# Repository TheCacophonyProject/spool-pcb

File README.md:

# Spool PCB

## Other bits to order

### DigiKey

- 2 x Crimped leads: [455-4118-ND](https://www.digikey.com/en/products/detail/jst-sales-america-inc/ASXASXA22K254/9951627) Can chop in half and use 2 of the ends for the motor and 2 for the magnet
- 1 x 8 Pin cable assembly [455-3842-ND](https://www.digikey.com/en/products/detail/jst-sales-america-inc/A08XAF08XAF22K203B/9922118) for connecting main and plug board.
- 3 x Protection Diodes [SS54-HF](https://www.digikey.com/en/products/detail/comchip-technology/SS54-HF/11584321) to be hand soldered onto the plug board.

### LCSC

- 2 x Photo interrupter [DY-ITR8402](https://www.lcsc.com/product-detail/C390039.html)
- 1 x 2 Pin JST XA housing [XAP-02V-1](https://www.lcsc.com/product-detail/C157892.html)
- 1 x 3 Pin JST XA housing [XAP-03V-1](https://www.lcsc.com/product-detail/C157891.html)
- 2 x 8 Pin JST XA Plug [S08B-XASK-1(LF)(SN)](https://www.lcsc.com/product-detail/C495695.html)
- 1 x Magnet rotary position sensor? Not too sure if this will end up being used or not. [AS5600-ASOT](https://www.lcsc.com/product-detail/C499458.html)

### JNICON

- 1 x 6 Pin Auxiliary plug (TODO: Add part number)
- 1 x 4 Pin Power plug (TODO: Add part number)

## Construction

TODO: Write construction/programming instructions.

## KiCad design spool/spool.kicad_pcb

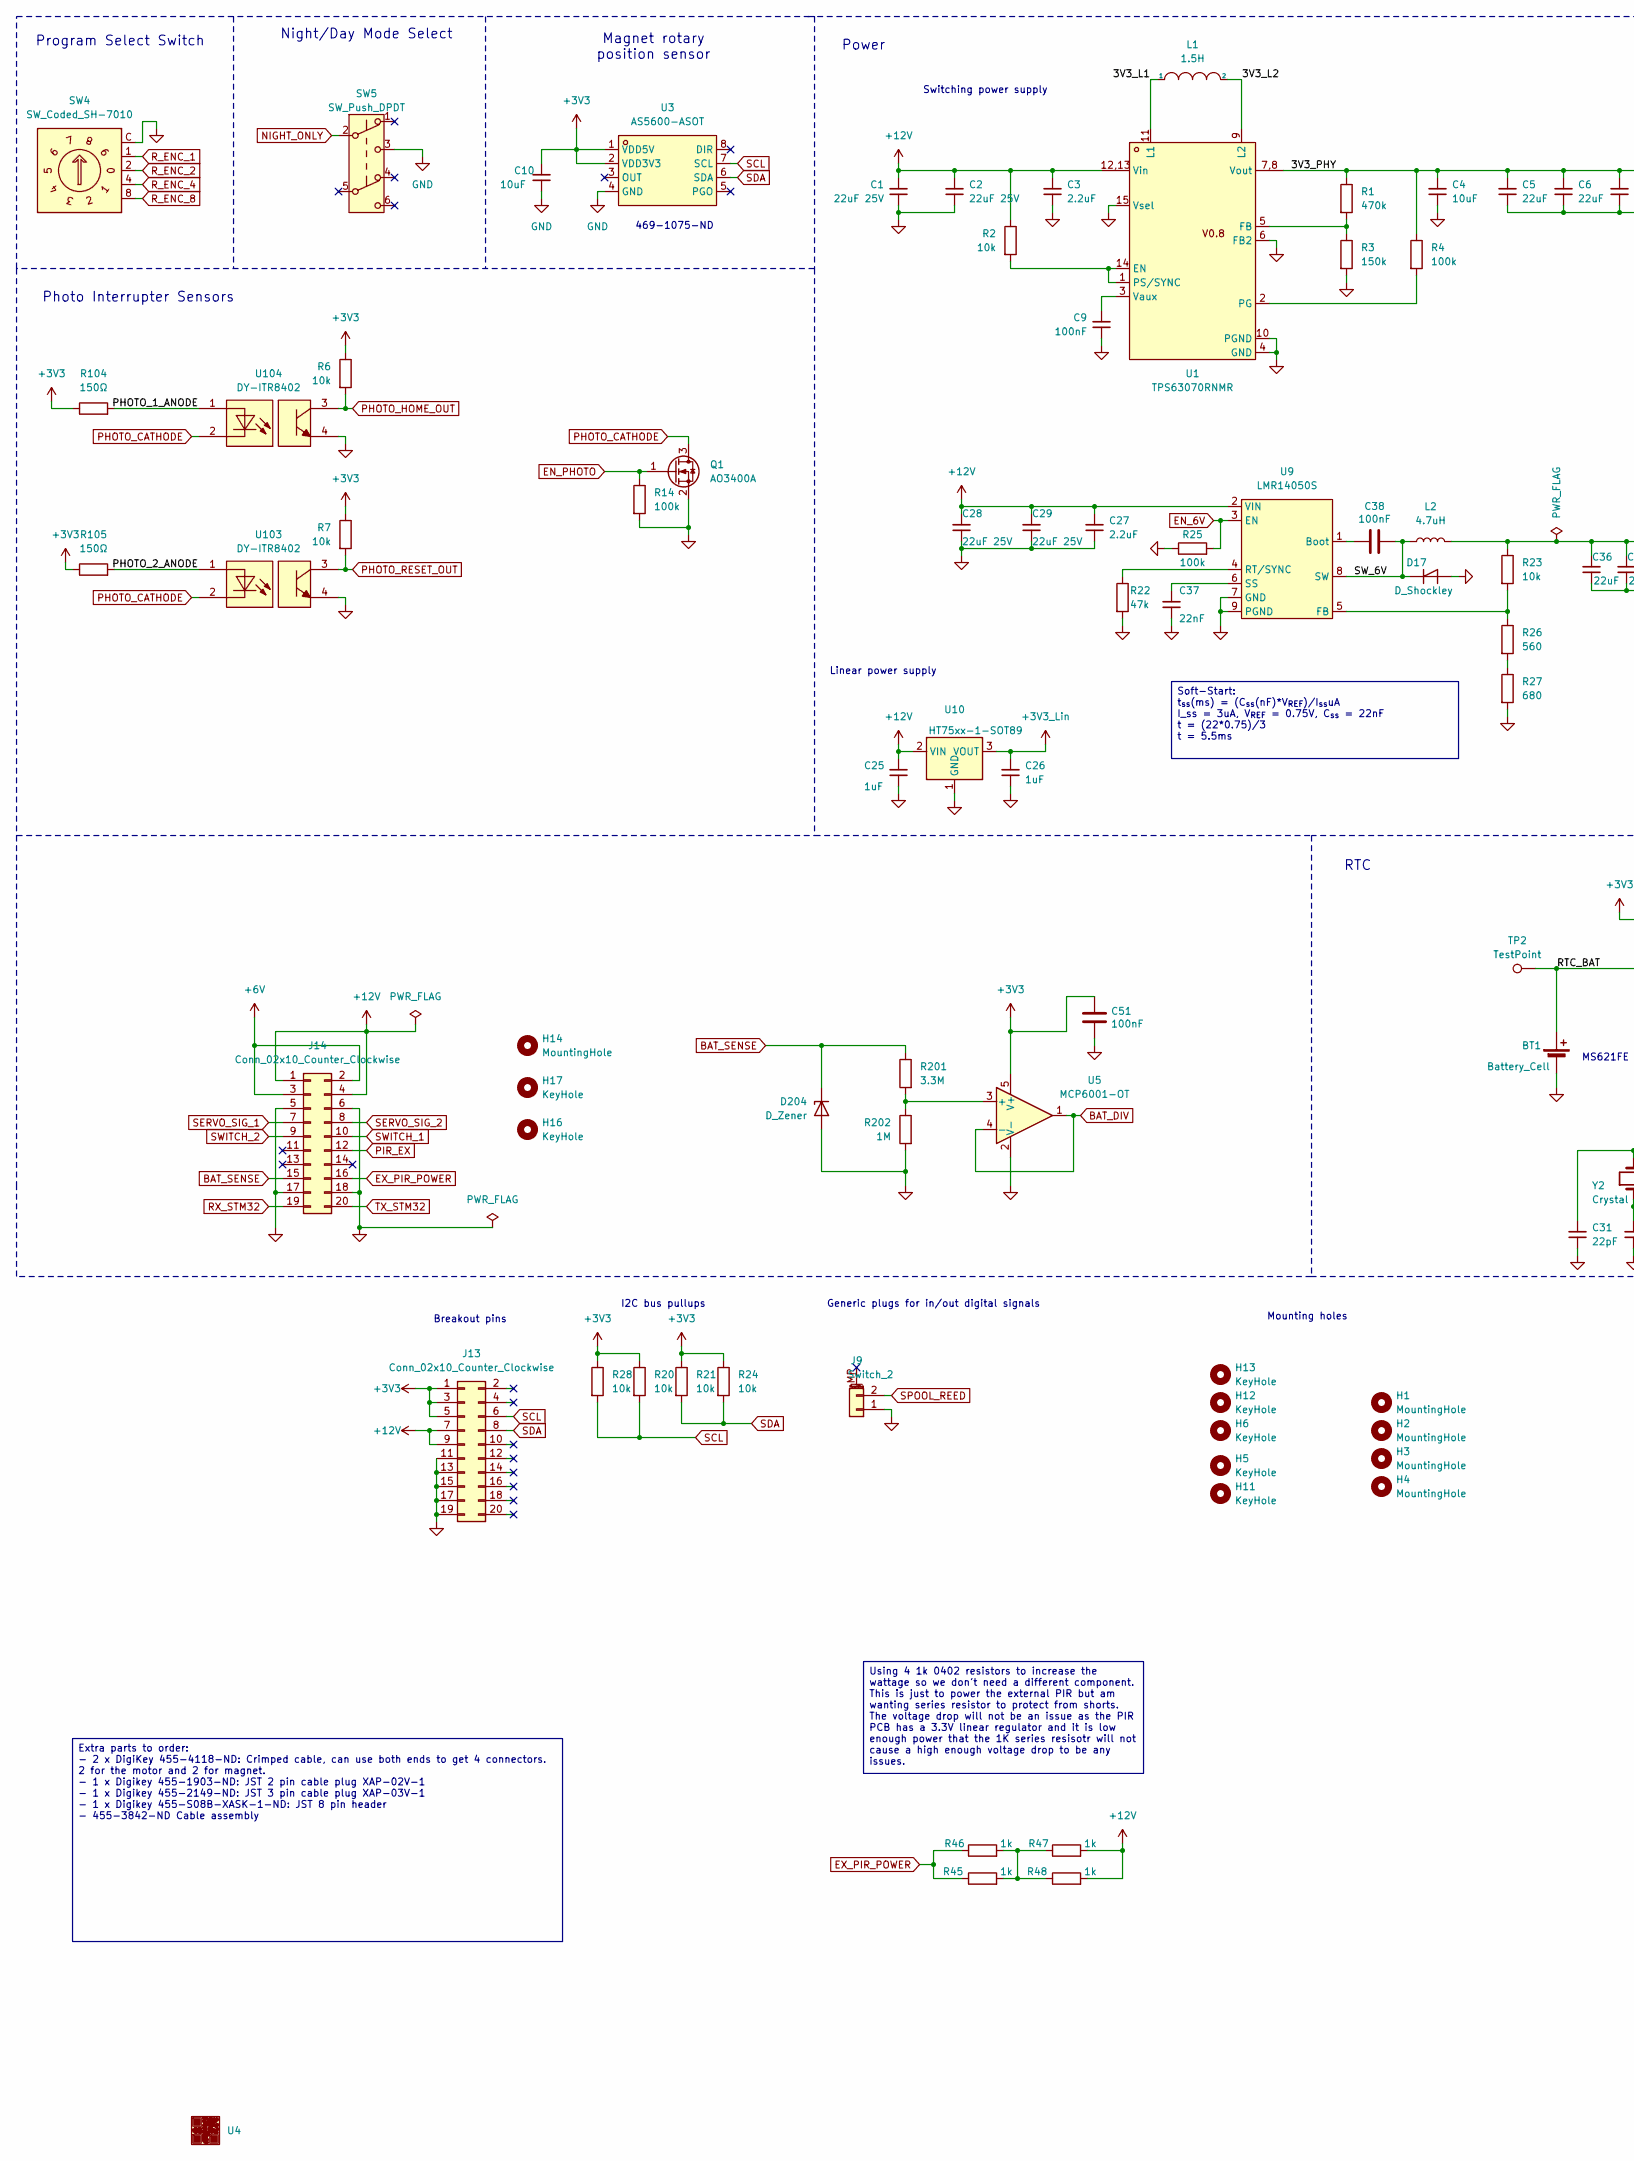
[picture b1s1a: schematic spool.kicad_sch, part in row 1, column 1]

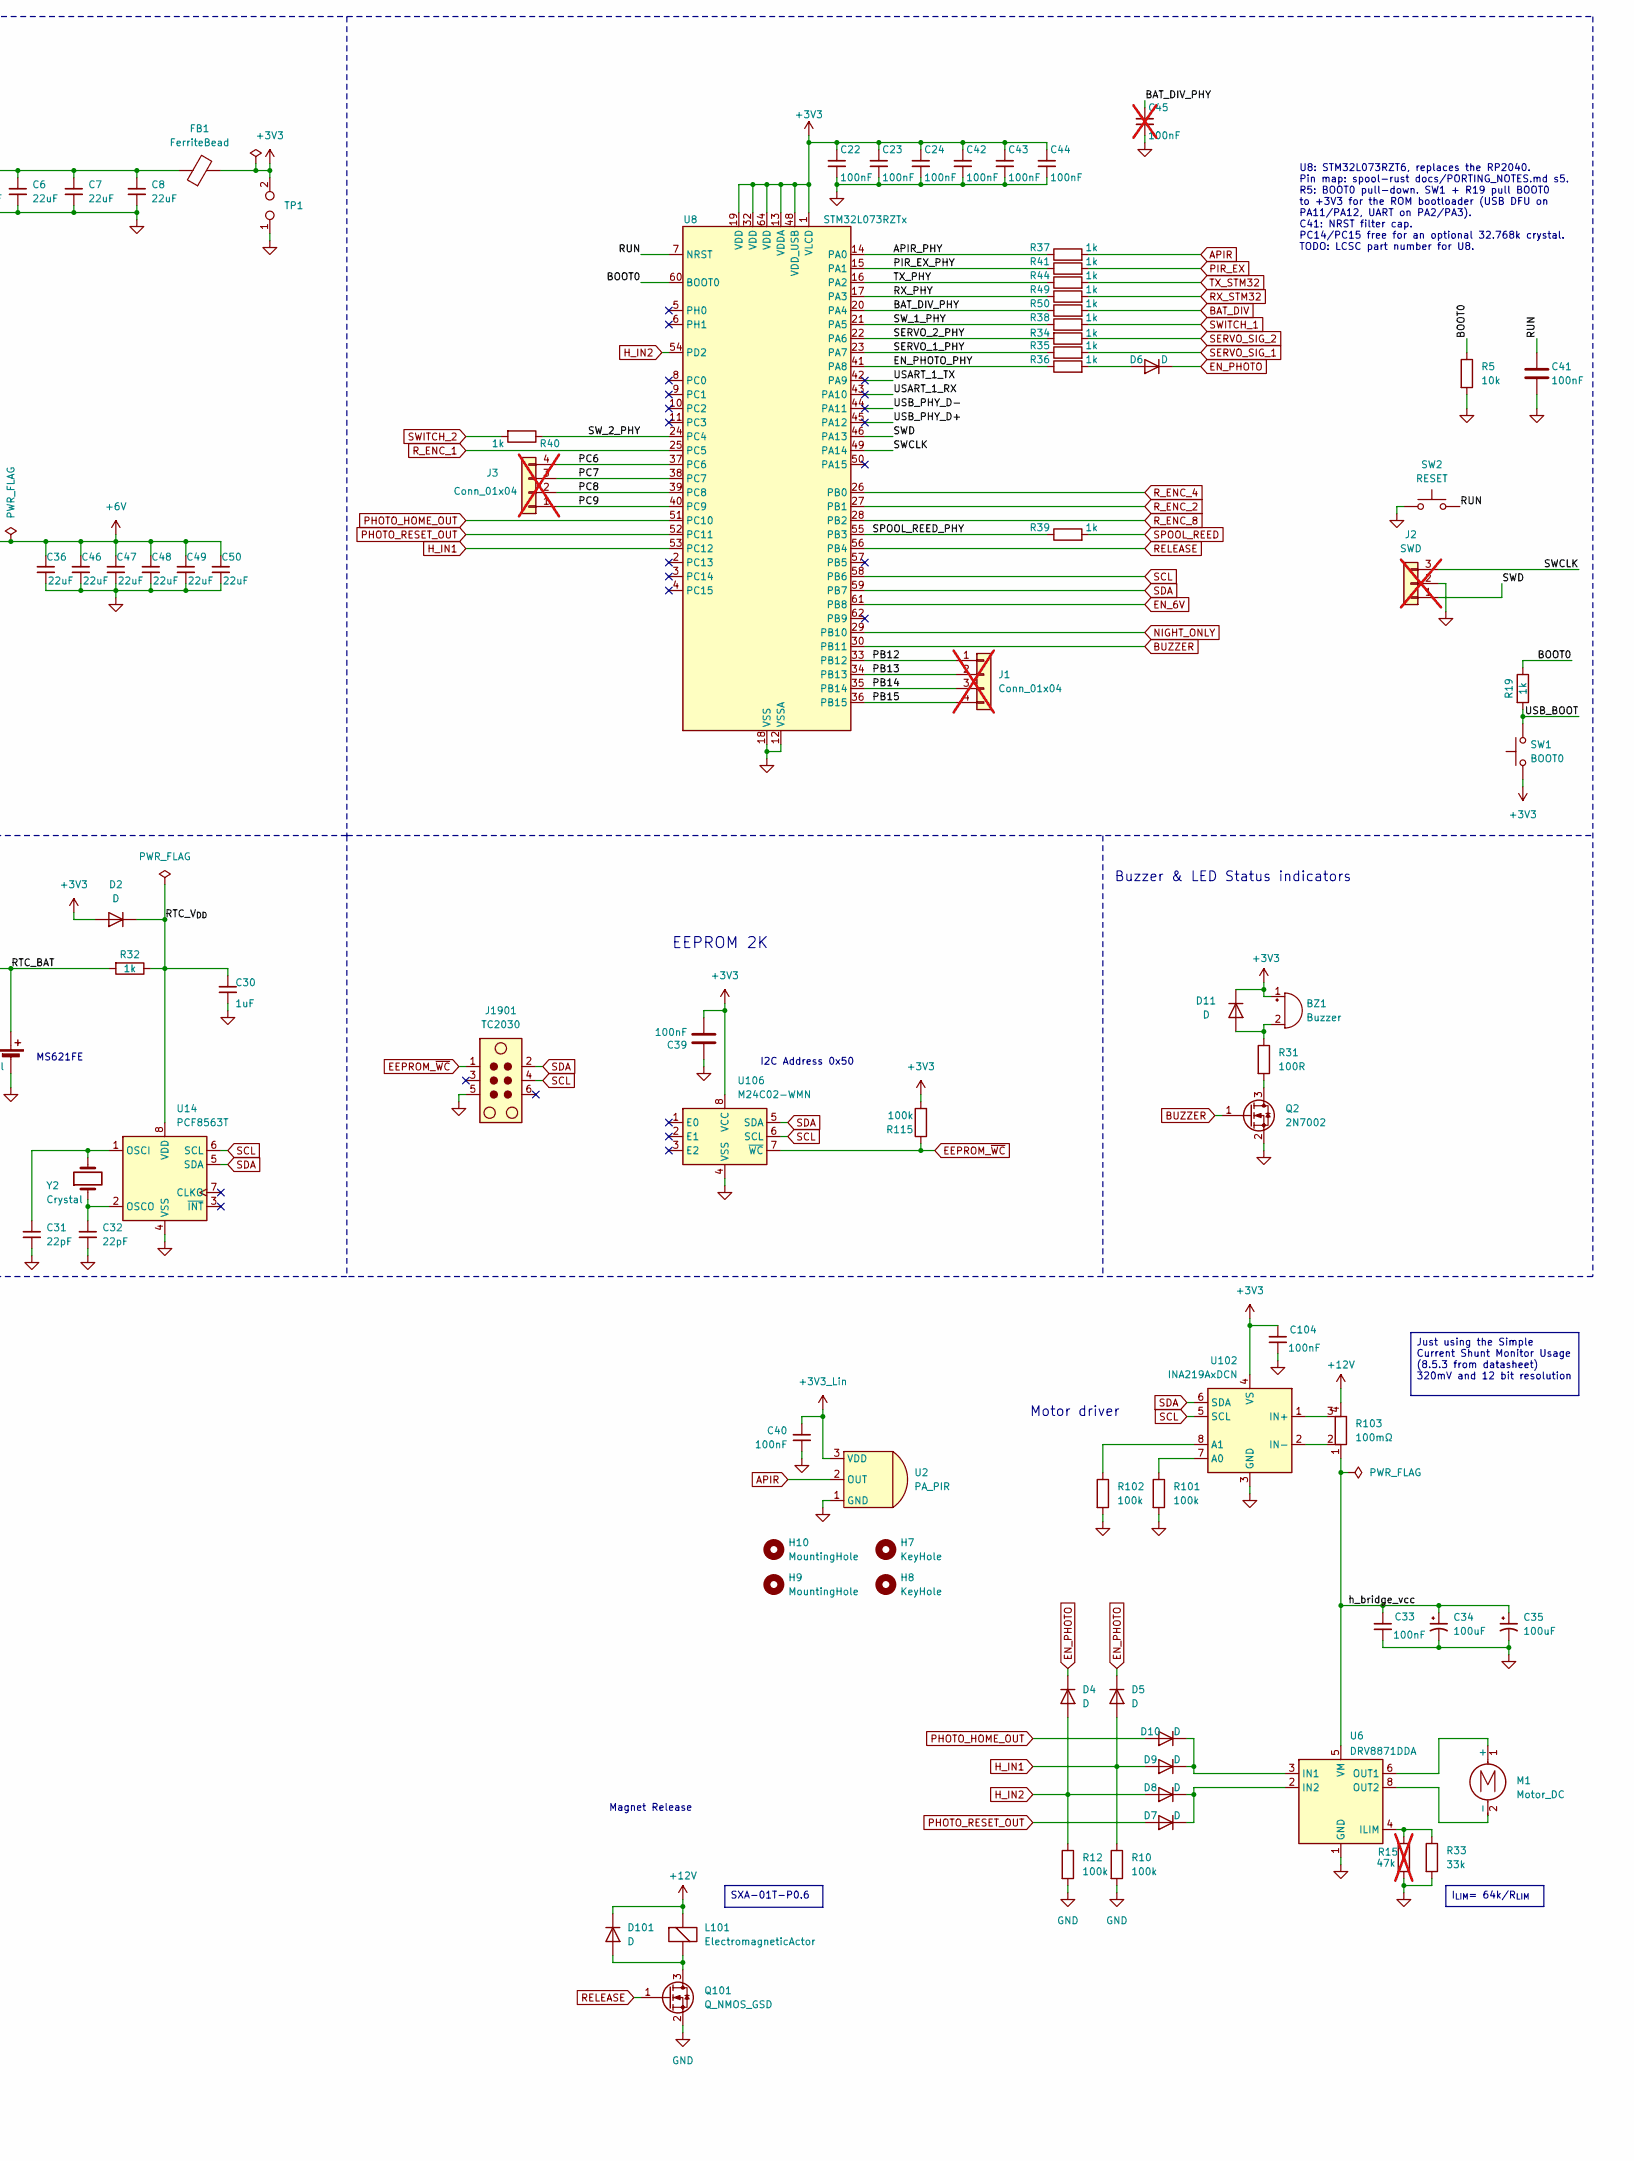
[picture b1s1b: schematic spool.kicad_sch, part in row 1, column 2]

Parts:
BT1: Battery_Cell; CAP-SMD_FL11E; LCSC Part C80909
BZ1: Buzzer; BUZ-TH_BD9.0-P4.00-D0.6-FD; LCSC Part C96256
C1, C2, C28, C29: 22uF 25V; C_0805_2012Metric; LCSC Part C45783
C3, C27: 2.2uF; C_0402_1005Metric; LCSC Part C159814
C4, C10: 10uF; C_0402_1005Metric; LCSC Part C15525
C5, C6, C7, C8, C36, C46, C47, C48, C49, C50: 22uF; C_0603_1608Metric; LCSC Part C86295
C9, C22, C23, C24, C33, C38, C39, C40, C41, C42, C43, C44, C51, C104: 100nF; C_0402_1005Metric; LCSC Part C307331
C25, C26, C30: 1uF; C_0402_1005Metric; LCSC Part C52923
C31, C32: 22pF; C_0402_1005Metric; LCSC Part C1555
C34, C35: 100uF; CP_Elec_6.3x7.7; LCSC Part C3338
C37: 22nF; C_0402_1005Metric; LCSC Part C1532
C45: 100nF; C_0402_1005Metric; LCSC Part C307331; not fitted
D2, D4, D5, D6, D7, D8, D9, D10, D11, D101: D; D_SOD-323; LCSC Part C2128
D17: D_Shockley; D_SMA; LCSC Part C22452
D204: D_Zener; D_SOD-123; LCSC Part C19077413
FB1: FerriteBead; L_0805_2012Metric; LCSC Part C76818
H1, H2, H3, H4, H9, H10, H14: MountingHole; MountingHole_3.5mm_M3
H5, H6, H7, H8, H11, H12, H13, H16, H17: KeyHole; 3.0mm_key_hole
J1, J3: Conn_01x04; PinHeader_1x04_P2.54mm_Vertical; not fitted
J2: SWD; PinHeader_1x03_P1.00mm_Vertical; not fitted
J9: Switch_2; JST_SH_BM02B-SRSS-TB_1x02-1MP_P1.00mm_Vertical; LCSC Part C160388
J13: Conn_02x10_Counter_Clockwise; test-headers
J14: Conn_02x10_Counter_Clockwise; PinSocket_2x10_P2.54mm_Vertical; LCSC Part C92266
J1901: TC2030; Tag-Connect_TC2030-IDC-NL_2x03_P1.27mm_Vertical
L1: 1.5H; L_1008_2520Metric; LCSC Part C2042459
L2: 4.7uH; IND-SMD_L7.0-W6.6; LCSC Part C408447
L101: ElectromagneticActor; JST_XA_B03B_2_Pin; LCSC Part C264992
M1: Motor_DC; JST_XA_B02B-XASK-1-A_1x02_P2.50mm_Vertical; LCSC Part C265077
Q1: AO3400A; SOT-23; LCSC Part C20917
Q2: 2N7002; SOT-23; LCSC Part C8545
Q101: Q_NMOS_GSD; SOT-23; LCSC Part C332302
R1: 470k; R_0402_1005Metric; LCSC Part C319591
R2, R5, R6, R7, R20, R21, R23, R24, R28: 10k; R_0402_1005Metric; LCSC Part C25744
R3: 150k; R_0402_1005Metric; LCSC Part C723770
R4, R10, R12, R14, R25, R101, R102, R115: 100k; R_0402_1005Metric; LCSC Part C25741
R15: 47k; R_Axial_DIN0204_L3.6mm_D1.6mm_P7.62mm_Horizontal; not fitted
R19, R32, R34, R35, R36, R37, R38, R39, R40, R41, R44, R45, R46, R47, R48, R49, R50: 1k; R_0402_1005Metric; LCSC Part C11702
R22: 47k; R_0402_1005Metric; LCSC Part C25792
R26: 560; R_0603_1608Metric; LCSC Part C23204
R27: 680; R_0603_1608Metric; LCSC Part C23228
R31: 100R; R_0402_1005Metric; LCSC Part C25076
R33: 33k; R_0805_2012Metric_Pad1.20x1.40mm_HandSolder; LCSC Part C17633
R103: 100mΩ; R_1206_Shunt; LCSC Part C25334
R104, R105: 150Ω; R_0603_1608Metric; LCSC Part C22808
R201: 3.3M; R_0603_1608Metric; LCSC Part C26096
R202: 1M; R_0603_1608Metric; LCSC Part C22935
SW1: BOOT0; SW_SPST_SKQG_WithStem; LCSC Part C318884
SW2: RESET; SW_SPST_SKQG_WithStem; LCSC Part C318884
SW4: SW_Coded_SH-7010; SW-TH_6P-L10.0-W10.0-P2.54-LS7.6_TSR-10; LCSC Part C51025675
SW5: SW_Push_DPDT; SW-TH_K3-2235D-F1; LCSC Part C189615
TP1: TestPoint_2Pole; test-point-2p
TP2: TestPoint; TestPoint_Loop_D1.80mm_Drill1.0mm_Beaded
U1: TPS63070RNMR; TPS63070; LCSC Part C109322
U2: PA_PIR
U3: AS5600-ASOT; SOIC-8_3.9x4.9mm_P1.27mm; LCSC Part C499458
U4: JLCPCB_QR_8mm
U5: MCP6001-OT; SOT-23-5; LCSC Part C29429
U6: DRV8871DDA; Texas_HTSOP-8-1EP_3.9x4.9mm_P1.27mm_EP2.95x4.9mm_Mask2.4x3.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; LCSC Part C75864
U8: STM32L073RZTx; LQFP-64_10x10mm_P0.5mm; LCSC Part C77160
U9: LMR14050S; TI_SO-PowerPAD-8; LCSC Part C155484
U10: HT75xx-1-SOT89; SOT-89-3; LCSC Part C14289
U14: PCF8563T; SOIC-8_3.9x4.9mm_P1.27mm; LCSC Part C7440
U102: INA219AxDCN; SOT-23-8; LCSC Part C87469
U103, U104: DY-ITR8402; OPTO-TH_DY-ITR8402; LCSC Part C390039
U106: M24C02-WMN; SOIC-8_3.9x4.9mm_P1.27mm; LCSC Part C7562
Y2: Crystal; Crystal_SMD_3215-2Pin_3.2x1.5mm; LCSC Part C32346

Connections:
+3V3: BZ1.1 (+), C10.1, C22.1, C23.1, C24.1, C39.2, C42.1, C43.1, C44.1, C51.1, C104.1, D2.2 (A), D11.1 (K), FB1.2, J13.1, J13.3, J13.5, R6.1, R7.1, R20.1, R21.1, R24.1, R28.1, R104.1, R105.1, R115.2, SW1.1, TP1.2, U3.1 (VDD5V), U3.2 (VDD3V3), U5.5 (V+), U8.1 (VLCD), U8.13 (VDDA), U8.19 (VDD), U8.32 (VDD), U8.48 (VDD_USB), U8.64 (VDD), U102.4 (VS), U106.8 (VCC)
+3V3_Lin: C26.1, C40.1, U2.3 (VDD), U10.3 (VOUT)
+6V: C36.1, C46.1, C47.1, C48.1, C49.1, C50.1, J14.2, J14.3, L2.2, R23.1
+12V: C1.1, C2.1, C3.1, C25.1, C27.1, C28.1, C29.1, D101.1 (K), J13.7, J13.9, J14.1, J14.4, L101.1 (-), R2.1, R47.2, R48.2, R103.4, U1.12,13 (Vin), U9.2 (VIN), U10.2 (VIN)
/3V3_L1: L1.1, U1.11 (L1)
/3V3_L2: L1.2, U1.9 (L2)
/3V3_PHY: C4.1, C5.1, C6.1, C7.1, C8.1, FB1.1, R1.1, R4.1, U1.7,8 (Vout)
/APIR_PHY: R37.1, U8.14 (PA0)
/BAT_DIV_PHY: C45.1, R50.1, U8.20 (PA4)
/BOOT0: R5.1, R19.1, U8.60 (BOOT0)
/EN_PHOTO_PHY: R36.1, U8.41 (PA8)
/PB12: J1.1, U8.33 (PB12)
/PB13: J1.2, U8.34 (PB13)
/PB14: J1.3, U8.35 (PB14)
/PB15: J1.4, U8.36 (PB15)
/PC6: J3.4, U8.37 (PC6)
/PC7: J3.3, U8.38 (PC7)
/PC8: J3.2, U8.39 (PC8)
/PC9: J3.1, U8.40 (PC9)
/PHOTO_1_ANODE: R104.2, U104.1
/PHOTO_2_ANODE: R105.2, U103.1
/PIR_EX_PHY: R41.1, U8.15 (PA1)
/RTC_BAT: BT1.1 (+), R32.2, TP2.1 (1_1)
/RTC_V_{DD}: C30.1, D2.1 (K), R32.1, U14.8 (VDD)
/RUN: C41.1, SW2.2, U8.7 (NRST)
/RX_PHY: R49.1, U8.17 (PA3)
/SERVO_1_PHY: R35.1, U8.23 (PA7)
/SERVO_2_PHY: R34.2, U8.22 (PA6)
/SPOOL_REED_PHY: R39.1, U8.55 (PB3)
/SWCLK: J2.3, U8.49 (PA14)
/SWD: J2.1, U8.46 (PA13)
/SW_1_PHY: R38.1, U8.21 (PA5)
/SW_2_PHY: R40.1, U8.24 (PC4)
/SW_6V: C38.1, D17.1 (K), L2.1, U9.8 (SW)
/TX_PHY: R44.1, U8.16 (PA2)
/USART_1_RX: U8.43 (PA10)
/USART_1_TX: U8.42 (PA9)
/USB_BOOT: R19.2, SW1.2
/USB_PHY_D+: U8.45 (PA12)
/USB_PHY_D-: U8.44 (PA11)
/h_bridge_vcc: C33.1, C34.1, C35.1, R103.1, U6.5 (VM)
APIR: R37.2, U2.2 (OUT)
BAT_DIV: R50.2, U5.1, U5.4 (-)
BAT_SENSE: D204.1 (K), J14.15, R201.1
BUZZER: Q2.1 (G), U8.30 (PB11)
EEPROM_~WC: J1901.1, R115.1, U106.7 (~WC)
EN_6V: R25.2, U8.61 (PB8), U9.3 (EN)
EN_PHOTO: D4.1 (K), D5.1 (K), D6.1 (K), Q1.1 (G), R14.1
EX_PIR_POWER: J14.16, R45.1, R46.1
GND: BT1.2 (-), C1.2, C2.2, C3.2, C4.2, C5.2, C6.2, C7.2, C8.2, C9.2, C10.2, C22.2, C23.2, C24.2, C25.2, C26.2, C27.2, C28.2, C29.2, C30.2, C31.2, C32.2, C33.2, C34.2, C35.2, C36.2, C37.2, C39.1, C40.2, C41.2, C42.2, C43.2, C44.2, C45.2, C46.2, C47.2, C48.2, C49.2, C50.2, C51.2, C104.2, D17.2 (A), D204.2 (A), J2.2, J9.1, J13.11, J13.13, J13.15, J13.17, J13.19, J14.5, J14.6, J14.17, J14.18, J1901.5, Q1.2 (S), Q2.2 (S), Q101.2 (S), R3.2, R5.2, R10.2, R12.2, R14.2, R15.2, R22.2, R25.1, R27.2, R33.2, R101.2, R102.2, R202.2, SW2.1, SW4.C, SW5.3 (C), TP1.1, U1.4 (GND), U1.6 (FB2), U1.10 (PGND), U1.15 (Vsel), U2.1 (GND), U3.4 (GND), U5.2 (V-), U6.1 (GND), U6.7 (GND), U6.9 (GND), U8.12 (VSSA), U8.18 (VSS), U8.31 (VSS), U8.47 (VSS), U8.63 (VSS), U9.7 (GND), U9.9 (PGND), U10.1 (GND), U14.4 (VSS), U102.3 (GND), U103.4, U104.4, U106.4 (VSS)
H_IN1: D5.2 (A), D9.2 (A), R10.1, U8.53 (PC12)
H_IN2: D4.2 (A), D8.2 (A), R12.1, U8.54 (PD2)
NIGHT_ONLY: SW5.2 (B), U8.29 (PB10)
unnamed: BZ1.2 (-), D11.2 (A), R31.1
unnamed: D6.2 (A), R36.2
unnamed: D7.1 (K), D8.1 (K), U6.2 (IN2)
unnamed: D9.1 (K), D10.1 (K), U6.3 (IN1)
unnamed: D101.2 (A), L101.2 (+), Q101.3 (D)
unnamed: M1.1 (+), U6.6 (OUT1)
unnamed: M1.2 (-), U6.8 (OUT2)
unnamed: Q2.3 (D), R31.2
unnamed: R26.2, R27.1
unnamed: R45.2, R46.2, R47.1, R48.1
unnamed: R2.2, U1.1 (PS/SYNC), U1.14 (EN)
unnamed: R1.2, R3.1, U1.5 (FB)
unnamed: R4.2, U1.2 (PG)
unnamed: C9.1, U1.3 (Vaux)
unnamed: R201.2, R202.1, U5.3 (+)
unnamed: R15.1, R33.1, U6.4 (ILIM)
unnamed: C38.2, U9.1 (Boot)
unnamed: R23.2, R26.1, U9.5 (FB)
unnamed: R22.1, U9.4 (RT/SYNC)
unnamed: C37.1, U9.6 (SS)
unnamed: C31.1, U14.1 (OSCI), Y2.2
unnamed: C32.1, U14.2 (OSCO), Y2.1
unnamed: R101.1, U102.7 (A0)
unnamed: R102.1, U102.8 (A1)
unnamed: R103.3, U102.1 (IN+)
unnamed: R103.2, U102.2 (IN-)
PHOTO_CATHODE: Q1.3 (D), U103.2, U104.2
PHOTO_HOME_OUT: D10.2 (A), R6.2, U8.51 (PC10), U104.3
PHOTO_RESET_OUT: D7.2 (A), R7.2, U8.52 (PC11), U103.3
PIR_EX: J14.12, R41.2
RELEASE: Q101.1 (G), U8.56 (PB4)
RX_STM32: J14.19, R49.2
R_ENC_1: SW4.1, U8.25 (PC5)
R_ENC_2: SW4.2, U8.27 (PB1)
R_ENC_4: SW4.4, U8.26 (PB0)
R_ENC_8: SW4.8, U8.28 (PB2)
SCL: J13.6, J1901.4, R20.2, R28.2, U3.7 (SCL), U8.58 (PB6), U14.6 (SCL), U102.5 (SCL), U106.6 (SCL)
SDA: J13.8, J1901.2, R21.2, R24.2, U3.6 (SDA), U8.59 (PB7), U14.5 (SDA), U102.6 (SDA), U106.5 (SDA)
SERVO_SIG_1: J14.7, R35.2
SERVO_SIG_2: J14.8, R34.1
SPOOL_REED: J9.2, R39.2
SWITCH_1: J14.10, R38.2
SWITCH_2: J14.9, R40.2
TX_STM32: J14.20, R44.2

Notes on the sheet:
Magnet Release
Breakout pins
I2C bus pullups
RTC
Program Select Switch
Photo Interrupter Sensors
Buzzer & LED Status indicators
Night/Day Mode Select
Switching power supply
469-1075-ND
Magnet rotary position sensor
Power
Linear power supply
U8: STM32L073RZT6, replaces the RP2040. Pin map: spool-rust docs/PORTING_NOTES.md s5. R5: BOOT0 pull-down. SW1 + R19 pull BOOT0 to +3V3 for the ROM bootloader (USB DFU on PA11/PA12, UART on PA2/PA3). C41: NRST filter cap. PC14/PC15 free for an optional 32.768k crystal. TODO: LCSC part number for U8.
MS621FE
Generic plugs for in/out digital signals
Mounting holes
I2C Address 0x50
Motor driver
EEPROM 2K
Using 4 1k 0402 resistors to increase the wattage so we don't need a different component. This is just to power the external PIR but am wanting series resistor to protect from shorts. The voltage drop will not be an issue as the PIR PCB has a 3.3V linear regulator and it is low enough power that th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
Extra parts to order: - 2 x DigiKey 455-4118-ND: Crimped cable, can use both ends to get 4 connectors. 2 for the motor and 2 for magnet. - 1 x Digikey 455-1903-ND: JST 2 pin cable plug XAP-02V-1 - 1 x Digikey 455-2149-ND: JST 3 pin cable plug XAP-03V-1 - 1 x Digikey 455-S08B-XASK-1-ND: JST 8 pin he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
Soft-Start: t_{ss}(ms) = (C_{ss}(nF)*V_{REF})/I_{ss}uA I_ss = 3uA, V_{REF} = 0.75V, C_{ss} = 22nF t = (22*0.75)/3 t = 5.5ms
Just using the Simple Current Shunt Monitor Usage (8.5.3 from datasheet) 320mV and 12 bit resolution
I_{LIM}= 64k/R_{LIM}
SXA-01T-P0.6

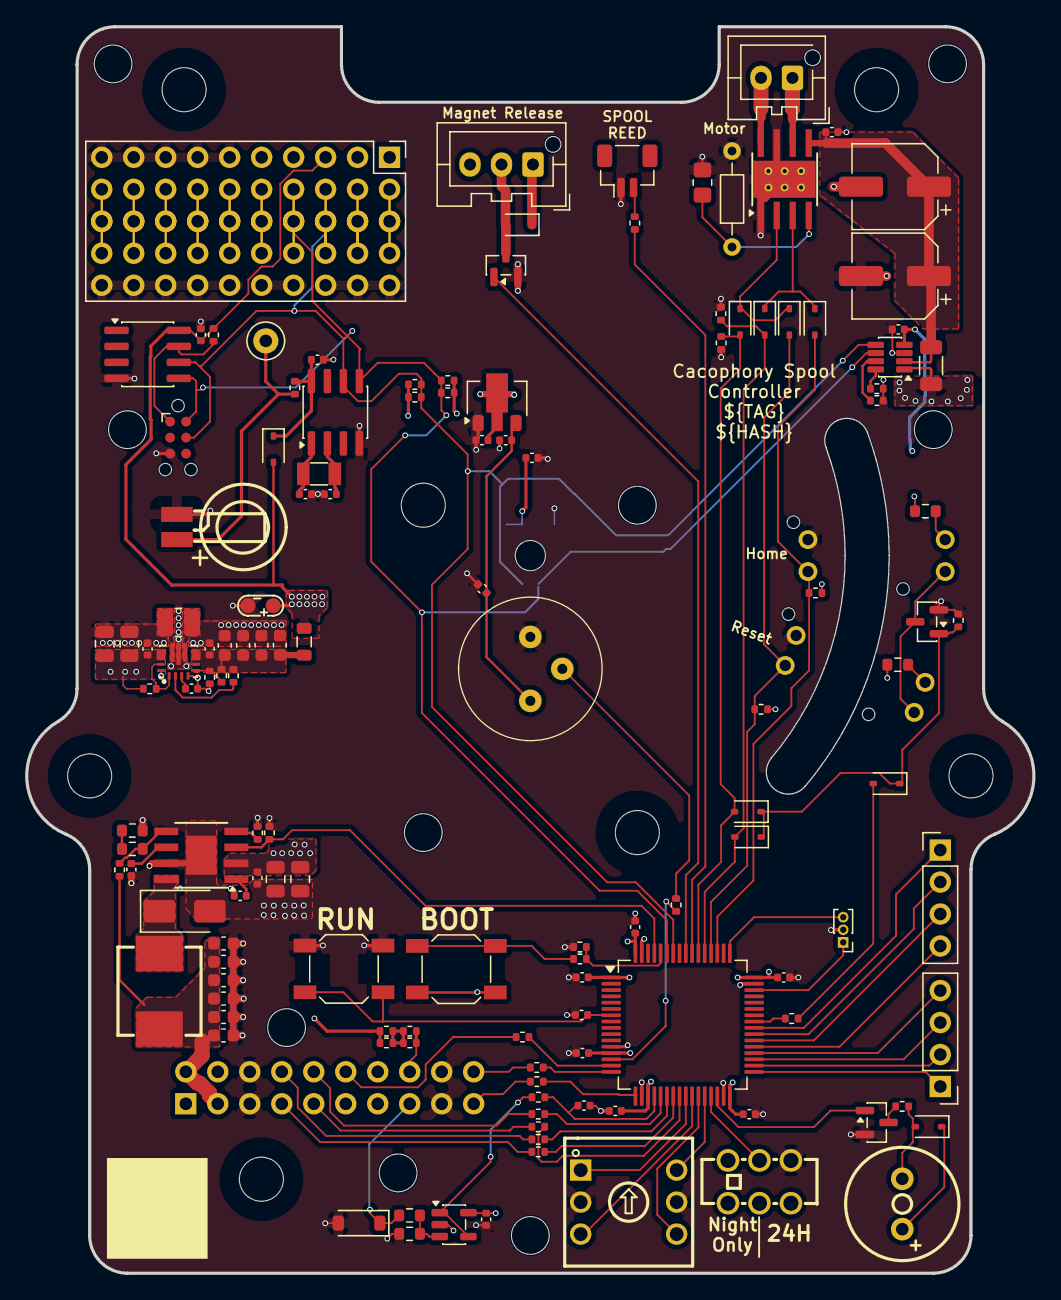
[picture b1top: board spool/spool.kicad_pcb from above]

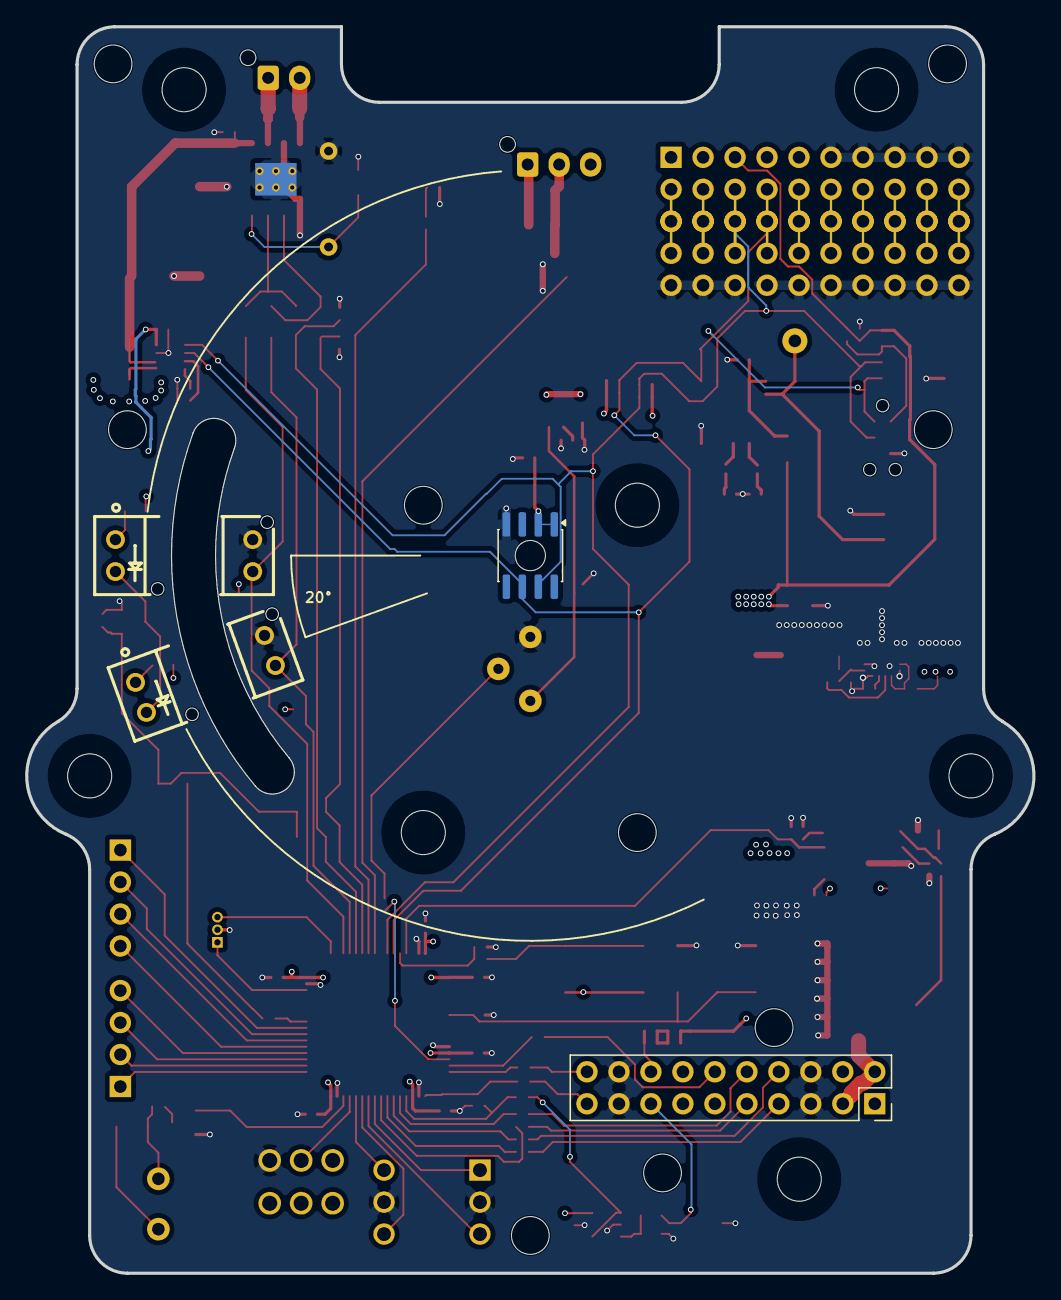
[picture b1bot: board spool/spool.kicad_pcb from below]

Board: 4 copper layers, 80.0 x 99.0 mm, 154 parts (4 on the bottom side), 93 nets.

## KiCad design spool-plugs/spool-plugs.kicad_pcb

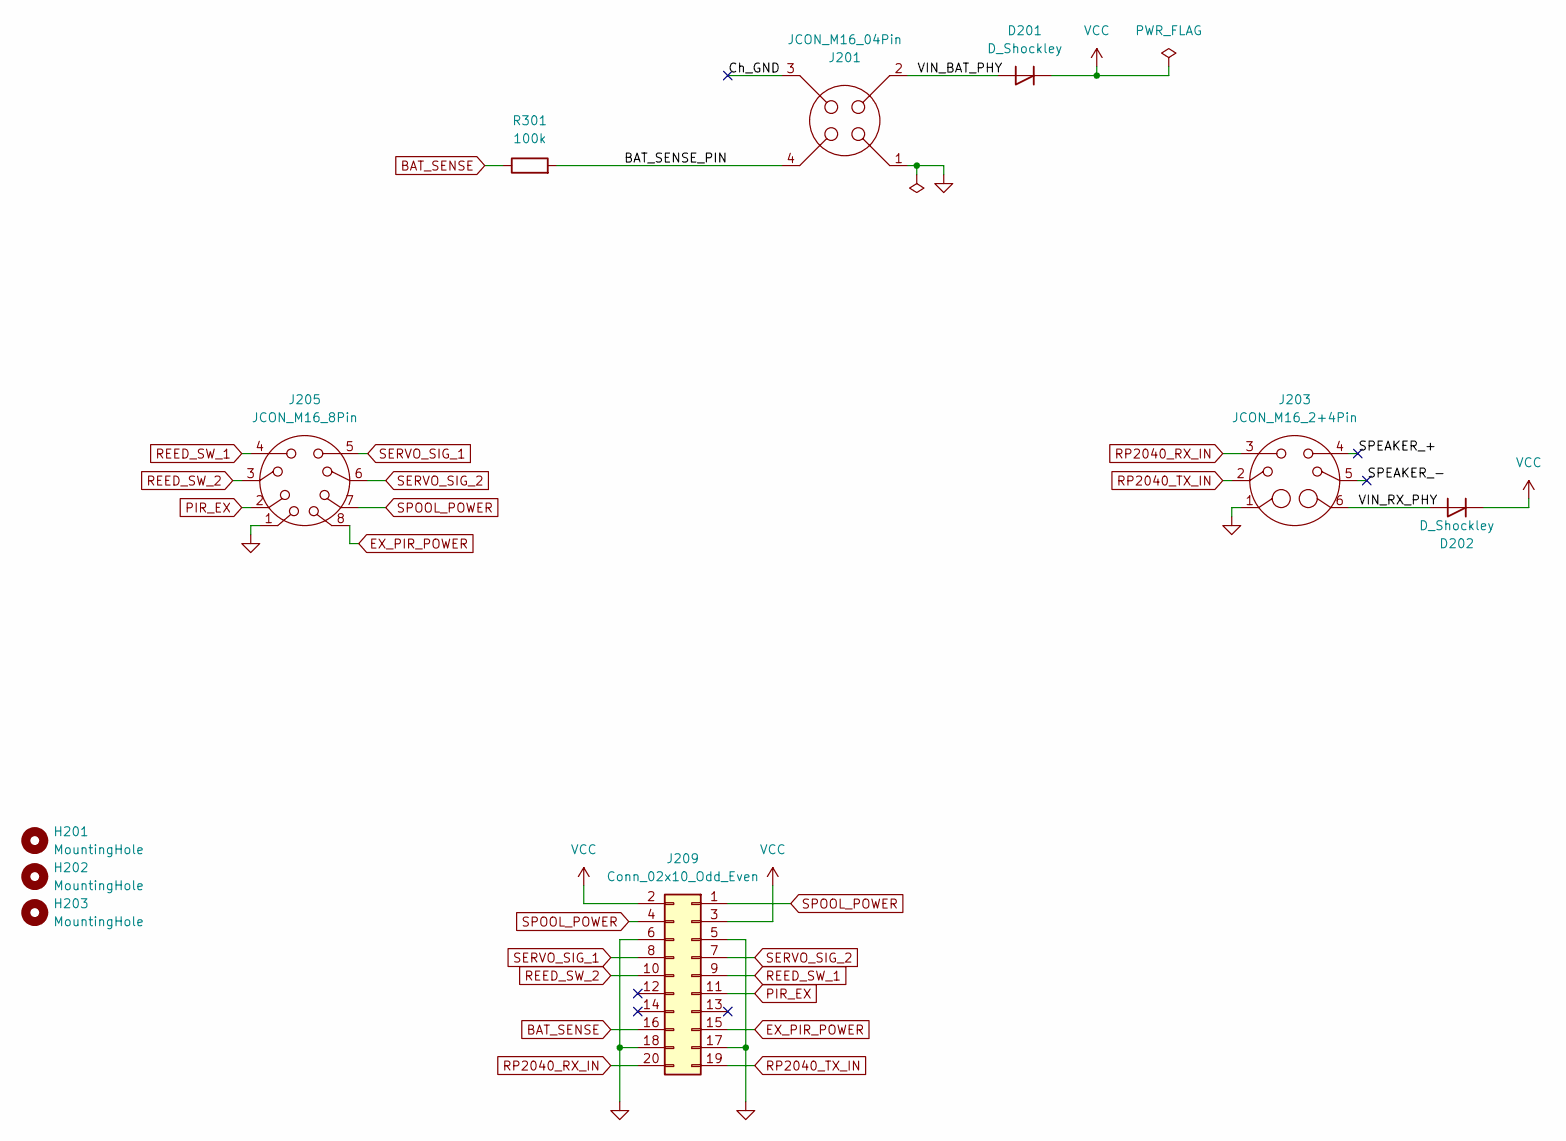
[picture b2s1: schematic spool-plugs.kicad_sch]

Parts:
D201, D202: D_Shockley; D_SMA_Handsoldering; Digikey 641-SS54-HFCT-ND
H201, H202, H203: MountingHole; 3.0mm_key_hole
J201: JCON_M16_04Pin; jcon-4pin_m16
J203: JCON_M16_2+4Pin; jcon-2+4pin-m16
J205: JCON_M16_8Pin; jcon-8pin-m16
J209: Conn_02x10_Odd_Even; spool_pcb-pcb_connector; LCSC Part C5383093
R301: 100k; R_0805_2012Metric_Pad1.20x1.40mm_HandSolder; LCSC Part C149504

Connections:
/BAT_SENSE_PIN: J201.4, R301.2
/Ch_GND: J201.3
/SPEAKER_+: J203.4
/SPEAKER_-: J203.5
/VIN_BAT_PHY: D201.2 (A), J201.2
/VIN_RX_PHY: D202.2 (A), J203.6
BAT_SENSE: J209.16, R301.1
EX_PIR_POWER: J205.8, J209.15
GND: J201.1, J203.1, J205.1, J209.5, J209.6, J209.17, J209.18
PIR_EX: J205.2, J209.11
REED_SW_1: J205.4, J209.9
REED_SW_2: J205.3, J209.10
RP2040_RX_IN: J203.3, J209.20
RP2040_TX_IN: J203.2, J209.19
SERVO_SIG_1: J205.5, J209.8
SERVO_SIG_2: J205.6, J209.7
SPOOL_POWER: J205.7, J209.1, J209.4
VCC: D201.1 (K), D202.1 (K), J209.2, J209.3

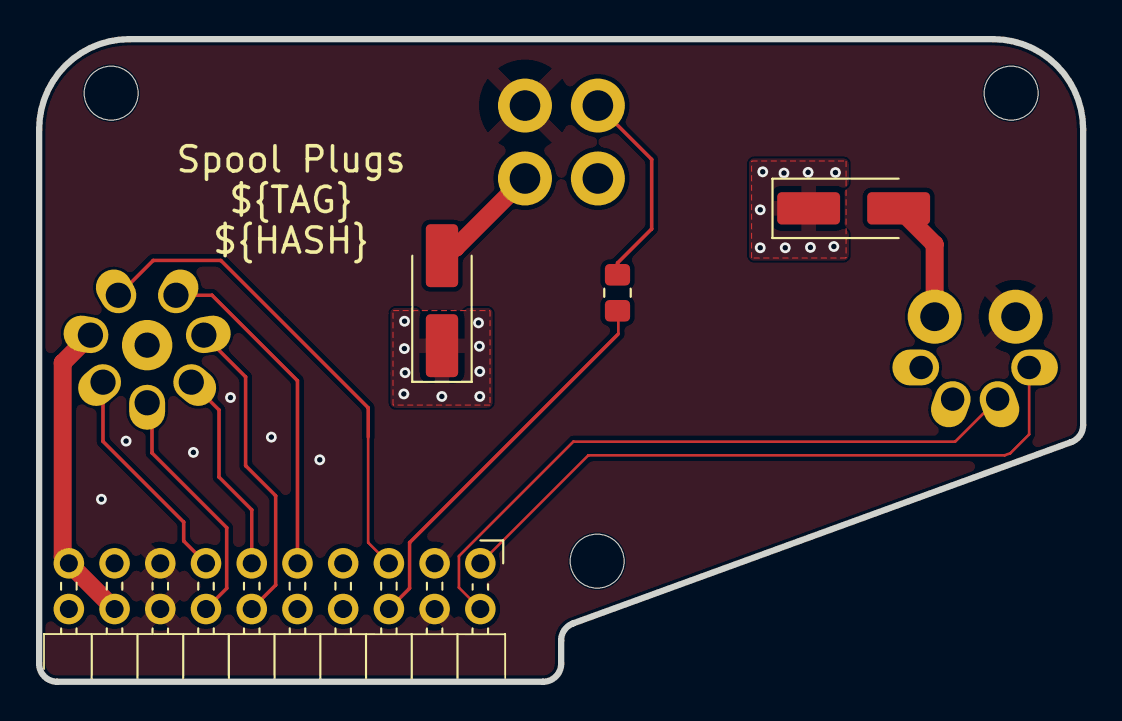
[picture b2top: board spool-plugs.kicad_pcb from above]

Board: 4 copper layers, 58.0 x 35.7 mm, 10 parts (0 on the bottom side), 15 nets.

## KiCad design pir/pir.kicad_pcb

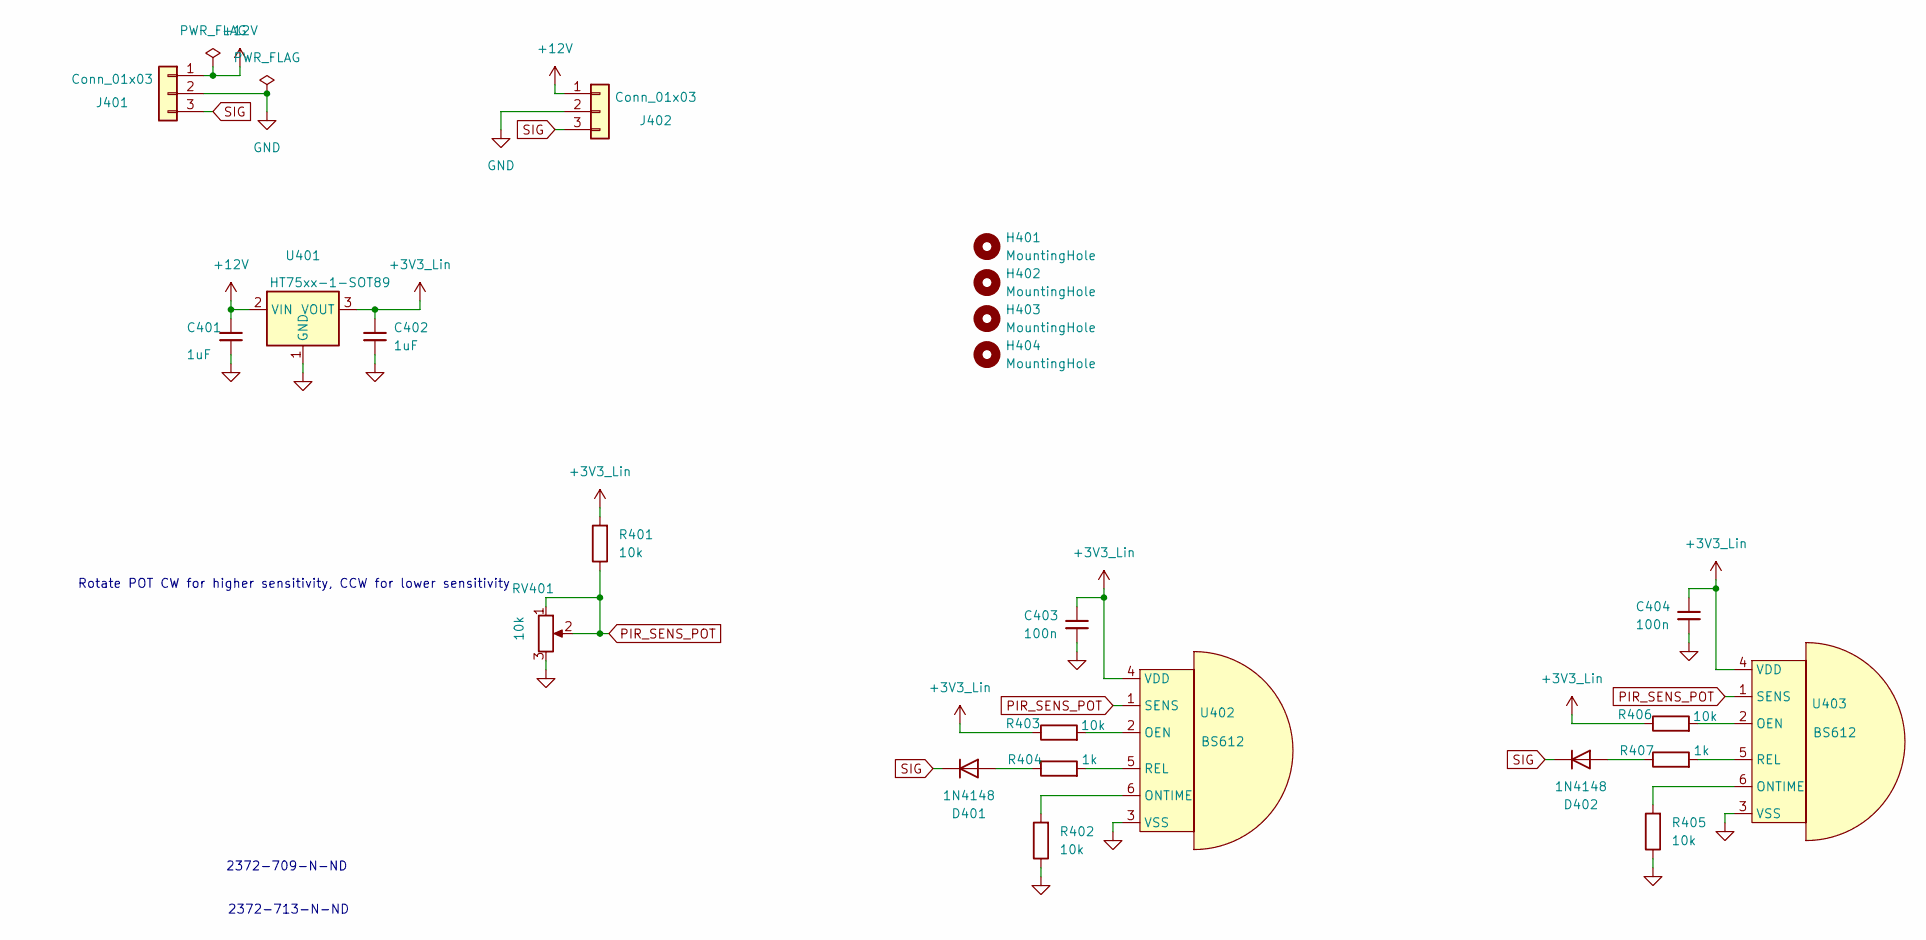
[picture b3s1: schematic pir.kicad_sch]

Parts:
C401, C402: 1uF; C_0603_1608Metric; LCSC Part C15849
C403, C404: 100n; C_0402_1005Metric; LCSC Part C307331
D401, D402: 1N4148; D_SOD-123; LCSC Part C81598
H401, H402, H403, H404: MountingHole; MountingHole_3.2mm_M3
J401, J402: Conn_01x03; JST_XA_S03B-XASK-1_1x03_P2.50mm_Horizontal; LCSC Part C491707
R401, R402, R403, R405, R406: 10k; R_0603_1608Metric; LCSC Part C25804
R404, R407: 1k; R_0603_1608Metric; LCSC Part C21190
RV401: 10k; RES-ADJ-TH_3362P; LCSC Part C58159
U401: HT75xx-1-SOT89; SOT-89-3; LCSC Part C14289
U402, U403: BS612; SENSORM-TH_BS612; LCSC Part C389589

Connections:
+3V3_Lin: C402.1, C403.1, C404.1, R401.2, R403.1, R406.1, U401.3 (VOUT), U402.4 (VDD), U403.4 (VDD)
+12V: C401.1, J401.1, J402.1, U401.2 (VIN)
GND: C401.2, C402.2, C403.2, C404.2, J401.2, J402.2, R402.1, R405.1, RV401.3, U401.1 (GND), U402.3 (VSS), U403.3 (VSS)
unnamed: D401.2 (A), R404.1
unnamed: D402.2 (A), R407.1
unnamed: R403.2, U402.2 (OEN)
unnamed: R402.2, U402.6 (ONTIME)
unnamed: R404.2, U402.5 (REL)
unnamed: R406.2, U403.2 (OEN)
unnamed: R405.2, U403.6 (ONTIME)
unnamed: R407.2, U403.5 (REL)
PIR_SENS_POT: R401.1, RV401.1, RV401.2, U402.1 (SENS), U403.1 (SENS)
SIG: D401.1 (K), D402.1 (K), J401.3, J402.3

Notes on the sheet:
2372-709-N-ND
Rotate POT CW for higher sensitivity, CCW for lower sensitivity
2372-713-N-ND

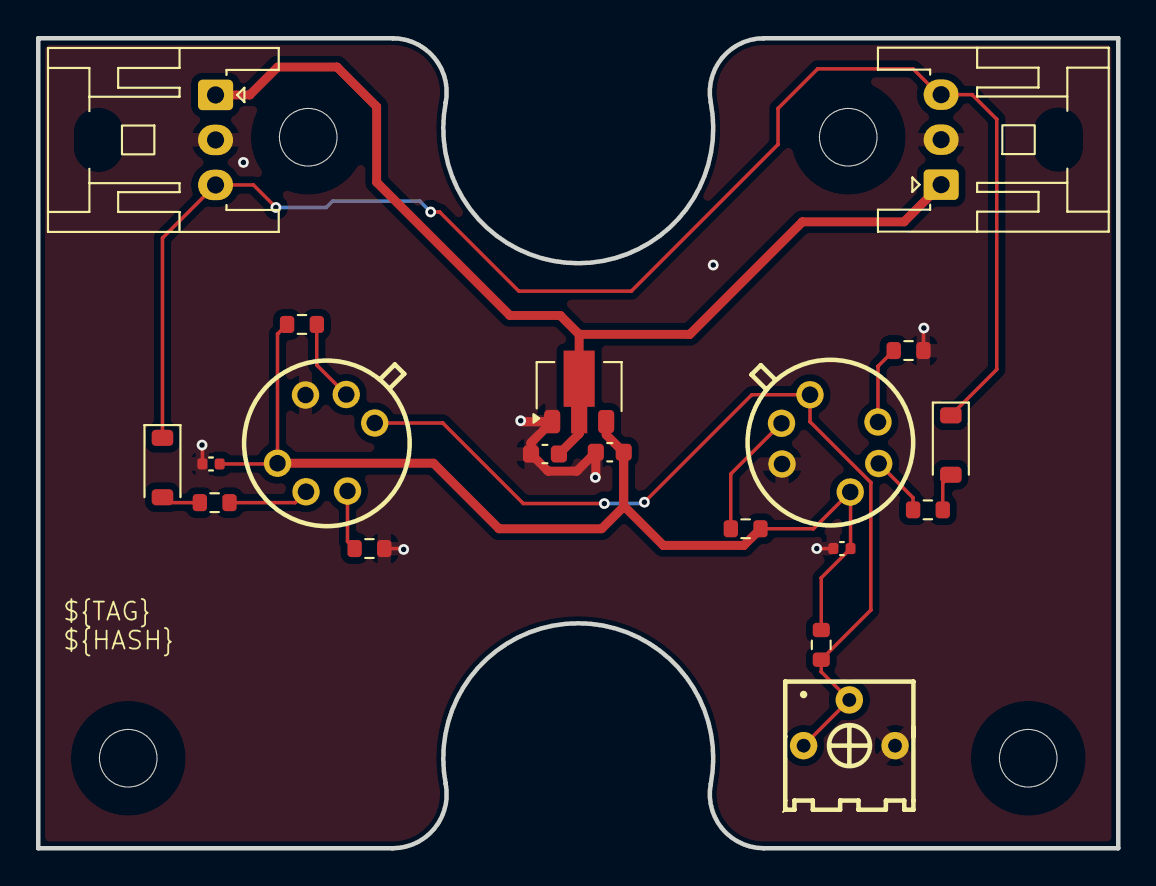
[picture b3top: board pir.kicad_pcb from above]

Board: 2 copper layers, 60.0 x 45.0 mm, 23 parts (0 on the bottom side), 13 nets.
